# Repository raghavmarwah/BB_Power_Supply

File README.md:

# Breadboard Power Supply

This is project #1 for the course [KiCAD like a Pro](https://techexplorations.com/so/kicad-like-a-pro-3rd-edition/). In this project, I created a PCB design to create a power supply module that readily connects to regular 830-tie and half-size breadboards.
<br><br>
More information about my progress with the course: https://raghavmarwah.com/kicad-udemy-course/
<br>

## Schematics

## 2 layer PCB

## 3D render (front)

## 3D render (rear)

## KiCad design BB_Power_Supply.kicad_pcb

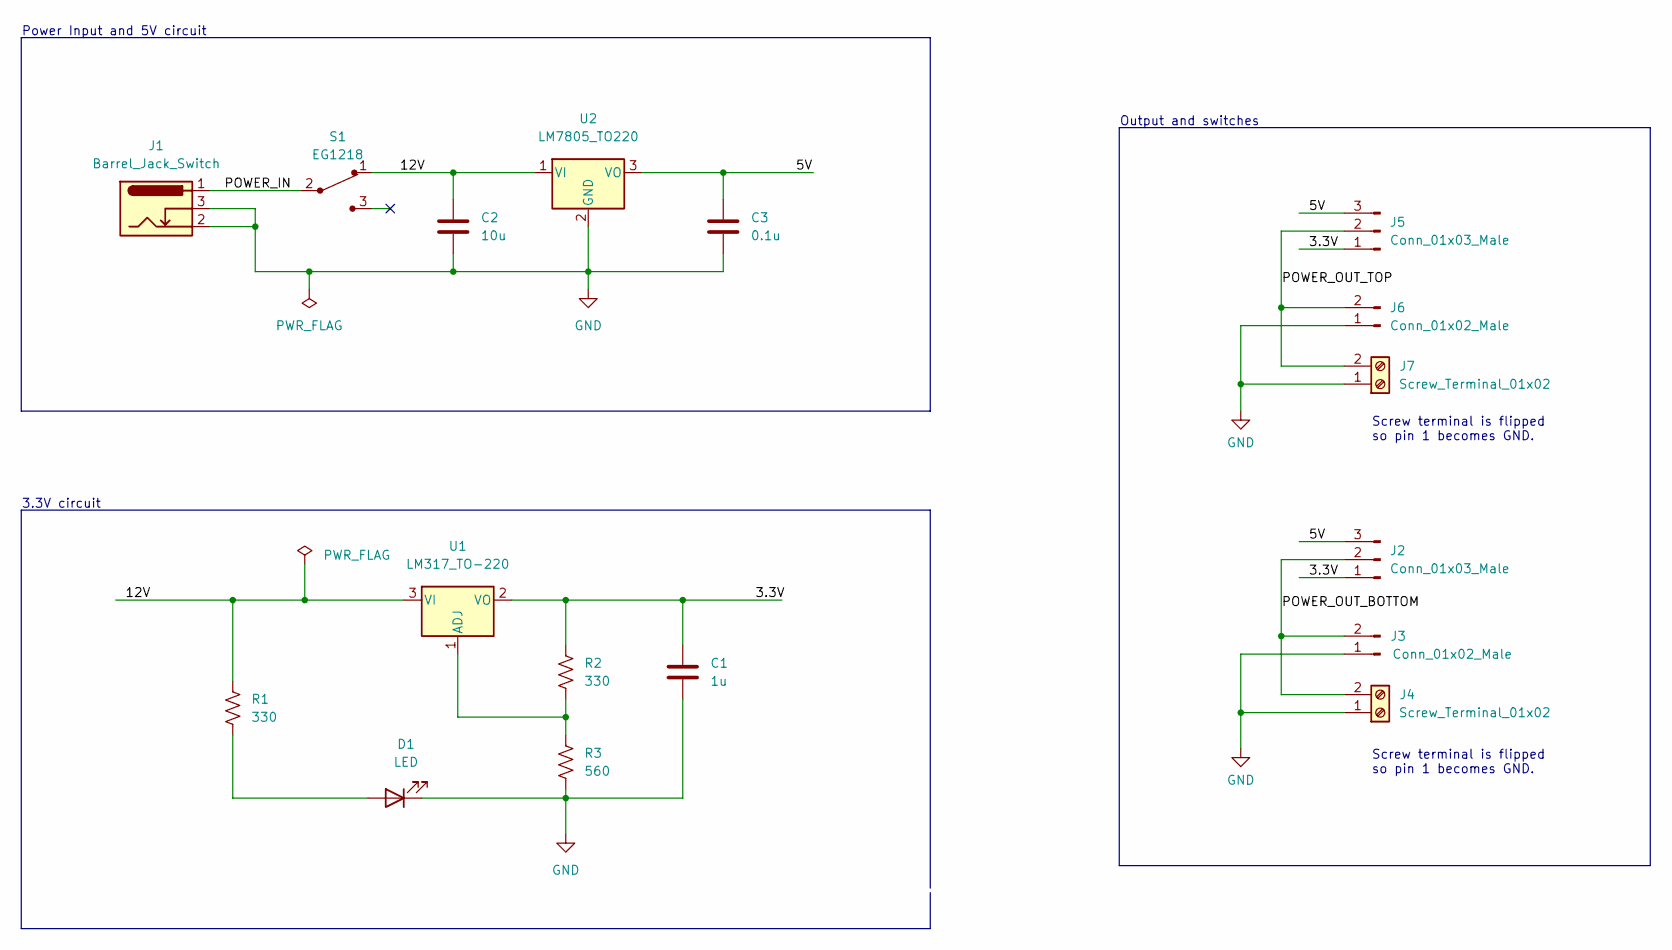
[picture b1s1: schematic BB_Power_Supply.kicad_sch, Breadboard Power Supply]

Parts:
C1: 1u; C_Disc_D3.0mm_W1.6mm_P2.50mm
C2: 10u; C_Disc_D3.0mm_W1.6mm_P2.50mm
C3: 0.1u; C_Disc_D3.0mm_W1.6mm_P2.50mm
D1: LED; LED_D5.0mm
J1: Barrel_Jack_Switch; BarrelJack_Horizontal
J2, J5: Conn_01x03_Male; PinHeader_1x03_P2.54mm_Vertical
J3, J6: Conn_01x02_Male; PinHeader_1x02_P2.54mm_Vertical
J4, J7: Screw_Terminal_01x02; TerminalBlock_bornier-2_P5.08mm
R1, R2: 330; R_Axial_DIN0204_L3.6mm_D1.6mm_P7.62mm_Horizontal
R3: 560; R_Axial_DIN0204_L3.6mm_D1.6mm_P7.62mm_Horizontal
S1: EG1218; Switch_Slide_11.6x4mm_EG1218; MPN EG1218; Digi-Key_PN EG1903-ND
U1: LM317_TO-220; TO-220-3_Vertical
U2: LM7805_TO220; TO-220-3_Vertical

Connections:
/3.3V: C1.1, J2.1, J5.1, R2.2, U1.2 (VO)
/5V: C3.1, J2.3, J5.3, U2.3 (VO)
/12V: C2.1, R1.2, S1.1, U1.3 (VI), U2.1 (VI)
/POWER_IN: J1.1, S1.2
/POWER_OUT_BOTTOM: J2.2, J3.2, J4.2
/POWER_OUT_TOP: J5.2, J6.2, J7.2
GND: C1.2, C2.2, C3.2, D1.1 (K), J1.2, J1.3, J3.1, J4.1, J6.1, J7.1, R3.1, U2.2 (GND)
unnamed: D1.2 (A), R1.1
unnamed: R2.1, R3.2, U1.1 (ADJ)

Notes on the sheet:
Screw terminal is flipped so pin 1 becomes GND.
Power Input and 5V circuit
3.3V circuit
Output and switches

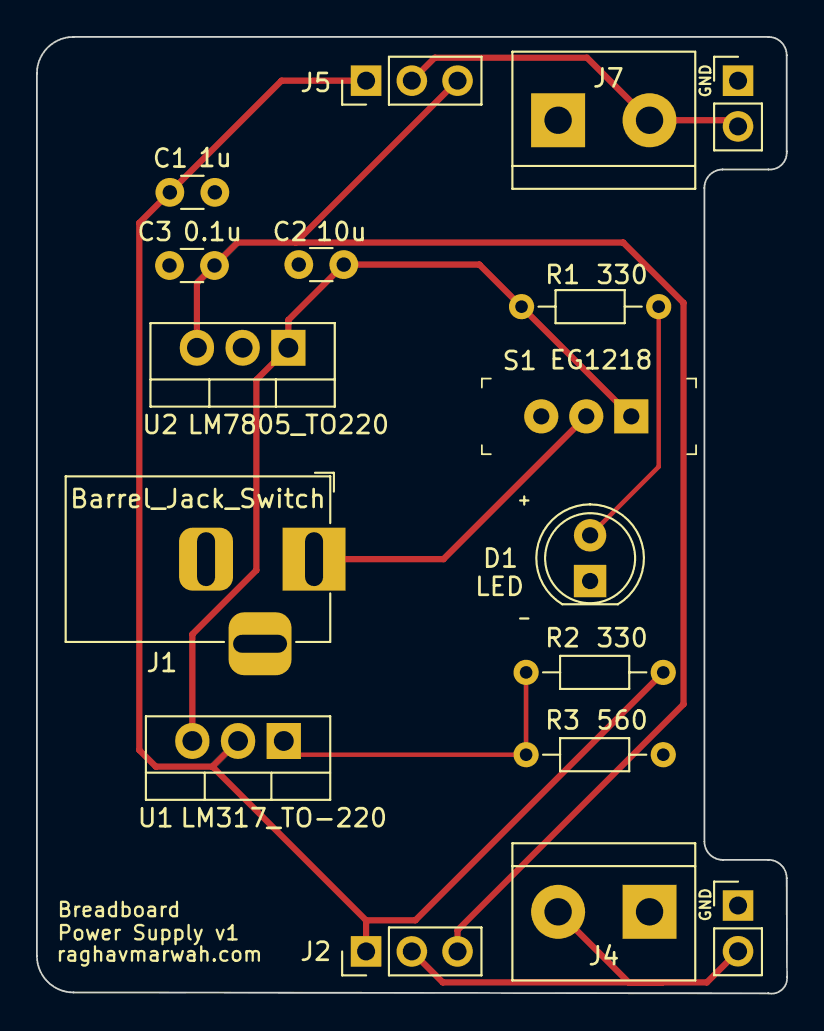
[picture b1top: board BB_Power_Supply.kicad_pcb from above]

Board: 2 copper layers, 41.7 x 53.2 mm, 17 parts (0 on the bottom side), 9 nets.

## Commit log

2022-08-28 Initial commit. Schematic completed.
2022-08-29 PCB design complete
2022-08-29 Fix issue with POWER_OUT net
2022-08-29 Final changes. Generated Gerber files.
2022-09-04 Created README.md
2022-09-04 Updated Sheet information in schematics
